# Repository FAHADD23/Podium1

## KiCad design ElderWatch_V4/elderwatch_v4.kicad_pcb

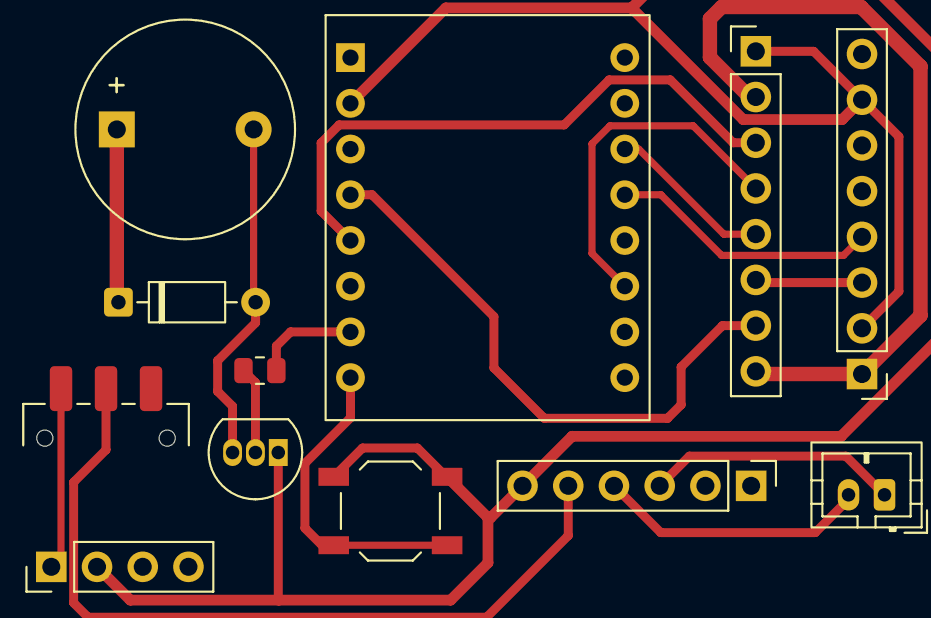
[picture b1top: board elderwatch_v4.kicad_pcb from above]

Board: 2 copper layers, 12 parts (0 on the bottom side), 17 nets.

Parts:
BT1: LiPo 3.7V 1000mAh; JST_PH_B2B-PH-K_1x02_P2.00mm_Vertical
BZ1: Active_Buzzer_5V; Buzzer_12x9.5RM7.6
D1: 1N4148; D_DO-35_SOD27_P7.62mm_Horizontal
DISP1: IPS_1.3_ST7789; PinHeader_1x08_P2.54mm_Vertical
Q1: S8050; TO-92_Inline
R1: 1k; R_0805_2012Metric
SW1: Power_Switch; SW_SPDT_CK_JS102011SAQN
SW2: SW_Cancel; SW_SPST_TL3342
U1: ESP32-C3_SuperMini; ESP32_C3_SuperMini
U2: MPU6050_GY-521; PinHeader_1x08_P2.54mm_Vertical
U3: TP4056_Module; PinHeader_1x06_P2.54mm_Vertical
U4: Boost_3.7V_to_5V; PinHeader_1x04_P2.54mm_Vertical

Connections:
+3V3: DISP1.2 (VCC), DISP1.8 (BLK), U2.1 (VCC)
+5V: BZ1.1 (+), D1.1 (K)
GND: DISP1.1 (GND), Q1.1 (E), SW2.1, U1.2 (GND), U2.2 (GND), U2.7 (AD0), U3.6 (OUT-), U4.2 (VIN-)
unnamed: BT1.1 (+), U3.3 (B+)
unnamed: BT1.2 (-), U3.4 (B-)
unnamed: BZ1.2 (-), D1.2 (A), Q1.3 (C)
unnamed: DISP1.7 (CS), U1.4 (GPIO4_CS)
unnamed: DISP1.6 (DC), U2.3 (SCL)
unnamed: DISP1.5 (RES/RST), U1.11 (GPIO7_RST)
unnamed: DISP1.3 (SCL/SCK), U1.5 (GPIO3_SCK)
unnamed: DISP1.4 (SDA/MOSI), U1.14 (GPIO10_MOSI)
unnamed: Q1.2 (B), R1.1
unnamed: SW1.1 (A), U4.1 (VIN+)
unnamed: SW2.2, U1.8 (GPIO0_BTN)
unnamed: R1.2, U1.7 (GPIO1_BUZZ)
unnamed: U1.12 (GPIO8_SDA), U2.4 (SDA)
VBAT: SW1.2 (B), U3.5 (OUT+)
